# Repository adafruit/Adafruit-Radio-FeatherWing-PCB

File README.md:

## Adafruit Radio FeatherWings PCB
<a href="http://www.adafruit.com/products/3229"><br/>
Click here to purchase one from the Adafruit shop</a>

Add short-hop wireless to your Feather with these RadioFruit Featherwings. These add-ons for any Feather board will let you integrate packetized radio (with the RFM69 radio) or LoRa radio (with the RFM9x's). These radios are good options for kilometer-range radio, and paired with one of our WiFi, cellular or Bluetooth Feathers, will let you bridge from 433/900 MHz to the Internet or y﻿our mobile ﻿device.

These radio modules come in four variants (two modulation types and two frequencies) The RFM69's are easiest to work with, and are well known and understood. The LoRa radios are exciting, longer-range and more powerful but also more expensive.

- [RFM69 @ 433 MHz](https://www.adafruit.com/products/3230) - basic packetized FSK/GFSK/MSK/GMSK/OOK radio at 433 MHz for use in Europe ITU 1 license-free ISM, or for amateur use with restrictions (check your local  amateur regulations!)
- [RFM69 @ 900 MHz](https://www.adafruit.com/products/3229) - basic packetized FSK/GFSK/MSK/GMSK/OOK radio at 868 or 915 MHz for use in Americas ITU 2 license-free ISM, or for amateur use with restrictions (check your amateur regulations!)
- [RFM98 @ 433 MHz](https://www.adafruit.com/products/3232) - LoRa capable radio at 433 MHz for use in Europe ITU 1 license-free ISM, or for amateur use with restrictions (check your local amateur regulations!)
- [RFM95 @ 900 MHz](https://www.adafruit.com/products/3231) - LoRa capable radio at 868 or 915 MHz for use in Americas ITU 2 license-free ISM, or for amateur use with restrictions (check your local amateur regulations!)

For more details, check out the product pages at

   * https://www.adafruit.com/products/3229
   * https://www.adafruit.com/products/3230
   * https://www.adafruit.com/products/3231
   * https://www.adafruit.com/products/3232
   
PCB files for the Adafruit Radio FeatherWing (RFM69 / RFM9x). The format is EagleCAD schematic and board layout

### License

Adafruit invests time and resources providing this open source design, please support Adafruit and open-source hardware by purchasing products from [Adafruit](https://www.adafruit.com)!

All text above must be included in any redistribution

Designed by Limor Fried/Ladyada for Adafruit Industries.
Creative Commons Attribution/Share-Alike, all text above must be included in any redistribution. 
See license.txt for additional information.

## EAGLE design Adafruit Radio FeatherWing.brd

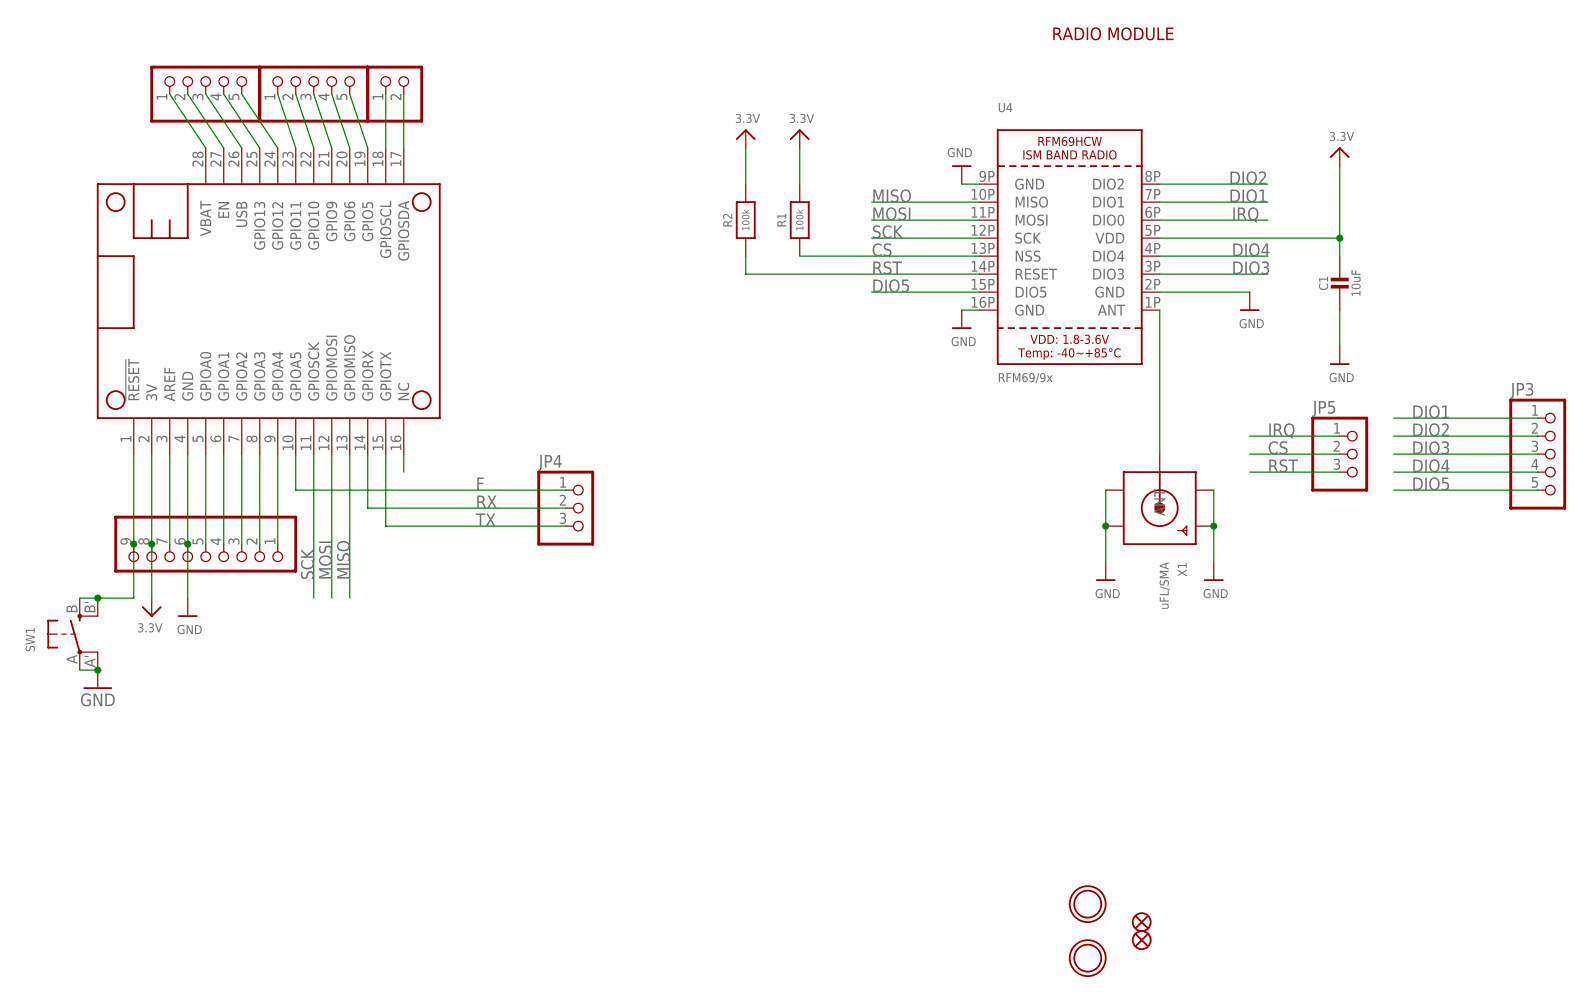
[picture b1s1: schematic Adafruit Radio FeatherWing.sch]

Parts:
C1: 10uF; 0805-NO
FID1, FID2: FIDUCIAL""; FIDUCIAL_1MM
JP1: HEADER-1X970MIL; 1X09_ROUND_70
JP2, JP3: HEADER-1X570MIL; 1X05_ROUND_70
JP4, JP5: HEADER-1X376MIL; 1X03_ROUND_76
JP6: HEADER-1X2ROUND; 1X02_ROUND
JP7: HEADER-1X576MIL; 1X05_ROUND_76
MS1: FEATHERWING_NOHOLES
R1, R2: 100k; 0603-NO
SW1: SWITCH_TACT_SMT4.6X2.8; BTN_KMR2_4.6X2.8
U4: RFM69/9x; RFMHCW_SMT
U$7, U$8: MOUNTINGHOLE2.5; MOUNTINGHOLE_2.5_PLATED
X1: uFL/SMA; SMA_EDGELAUNCH_UFL

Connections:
3.3V: C1.1, JP1.8, MS1.2 (3V), R1.2, R2.2, U4.5P (VDD)
A: JP7.1, MS1.23 (GPIO11)
ANT: U4.1P (ANT), X1.P (ANT)
B: JP7.2, MS1.22 (GPIO10)
C: JP7.3, MS1.21 (GPIO9)
CS: JP5.2, R1.1, U4.13P (NSS)
D: JP7.4, MS1.20 (GPIO6)
DIO1: JP3.1, U4.7P (DIO1)
DIO2: JP3.2, U4.8P (DIO2)
DIO3: JP3.3, U4.3P (DIO3)
DIO4: JP3.4, U4.4P (DIO4)
DIO5: JP3.5, U4.15P (DIO5)
E: JP7.5, MS1.19 (GPIO5)
EN: JP2.2, MS1.27 (EN)
F: JP4.1, MS1.10 (GPIOA5)
G: JP2.5, MS1.24 (GPIO12)
GND: C1.2, JP1.6, MS1.4 (GND), SW1.A, SW1.A' (P1), U4.2P (GND), U4.9P (GND), U4.16P (GND), X1.GND@1 (GND1), X1.GND@2 (GND2), X1.GND@3 (GND3), X1.GND@4 (GND4)
H: JP2.4, MS1.25 (GPIO13)
I: JP1.5, MS1.5 (GPIOA0)
IRQ: JP5.1, U4.6P (DIO0)
J: JP1.4, MS1.6 (GPIOA1)
K: JP1.3, MS1.7 (GPIOA2)
L: JP1.2, MS1.8 (GPIOA3)
M: JP1.1, MS1.9 (GPIOA4)
MISO: MS1.13 (GPIOMISO), U4.10P (MISO)
MOSI: MS1.12 (GPIOMOSI), U4.11P (MOSI)
unnamed: JP1.7, MS1.3 (AREF)
unnamed: JP1.9, MS1.1 (!RESET), SW1.B (S), SW1.B' (S1)
NC: MS1.16 (NC)
RST: JP5.3, R2.1, U4.14P (RESET)
RX: JP4.2, MS1.14 (GPIORX)
SCK: MS1.11 (GPIOSCK), U4.12P (SCK)
SCL: JP6.1, MS1.18 (GPIOSCL)
SDA: JP6.2, MS1.17 (GPIOSDA)
TX: JP4.3, MS1.15 (GPIOTX)
USB: JP2.3, MS1.26 (USB)
VBAT: JP2.1, MS1.28 (VBAT)

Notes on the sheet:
RADIO MODULE

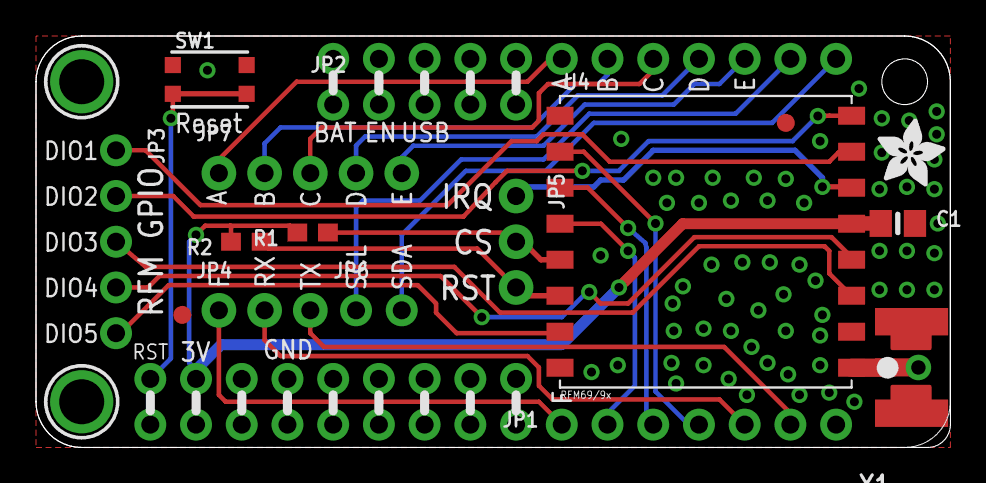
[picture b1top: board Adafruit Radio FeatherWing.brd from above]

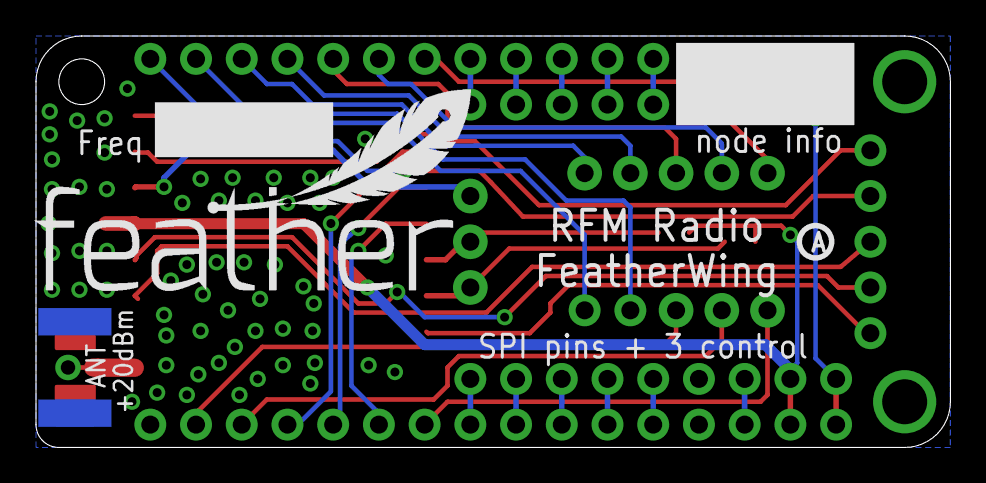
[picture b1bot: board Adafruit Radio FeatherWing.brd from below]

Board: 2 copper layers, 50.8 x 22.9 mm, 21 parts (2 on the bottom side), 36 nets.

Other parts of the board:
U$14: PCBFEAT-REV-040
U$15: ADAFRUIT_3.5MM
U$16: FEATHERLOGO

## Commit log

2016-08-24 init!

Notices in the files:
parts and their libraries:
microbuilder: This work is placed in the public domain, and may be freely used for commercial and non-commercial work with the following conditions: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
